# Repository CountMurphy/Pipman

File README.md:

Pipman Propeller watch
======================

The Pipman is a GPS average intelligence (not dumb, but not quit smart like pebble) watch that runs on the propeller platform.  It boasts:

* 1 Gb internal memory (for saving calendar info and saving GPS coordinates)
* GPS (with time syncing abilities, can get local time anywhere in the world)
* Tilt Compensated Compass
* Temperature reader
* Color Screen
* Calendar
* USB support

Note: The current code is beta ( I'm not going to pretend all of it is clean. Some parts are rubbish.  You know it, I know it, lets move on) and hardware specific. It can be easily tweaked to suit your needs, but if you want to create the watch exactly as is the parts are as follows:

* A 4d systems oled-128-G1 (http://old.4dsystems.com.au/prod.php?id=78)  (the G2 should work too)
* Any NEMA Gps (though for the PCB designs I used this one: http://www.mouser.com/ProductDetail/4D-Systems/GPS-PA6B/?qs=0tg2fxsCAusQqyNQtvdH%252bA%3D%3D)
* The Honeywell hmc6343 (http://www.digikey.com/product-detail/en/HMC6343/342-1056-ND/1692480.  If you know how to tweak I2C code it wouldn't be hard to get any compass moduel to work)
* 5 way switch for navigation (http://www.adafruit.com/products/504)

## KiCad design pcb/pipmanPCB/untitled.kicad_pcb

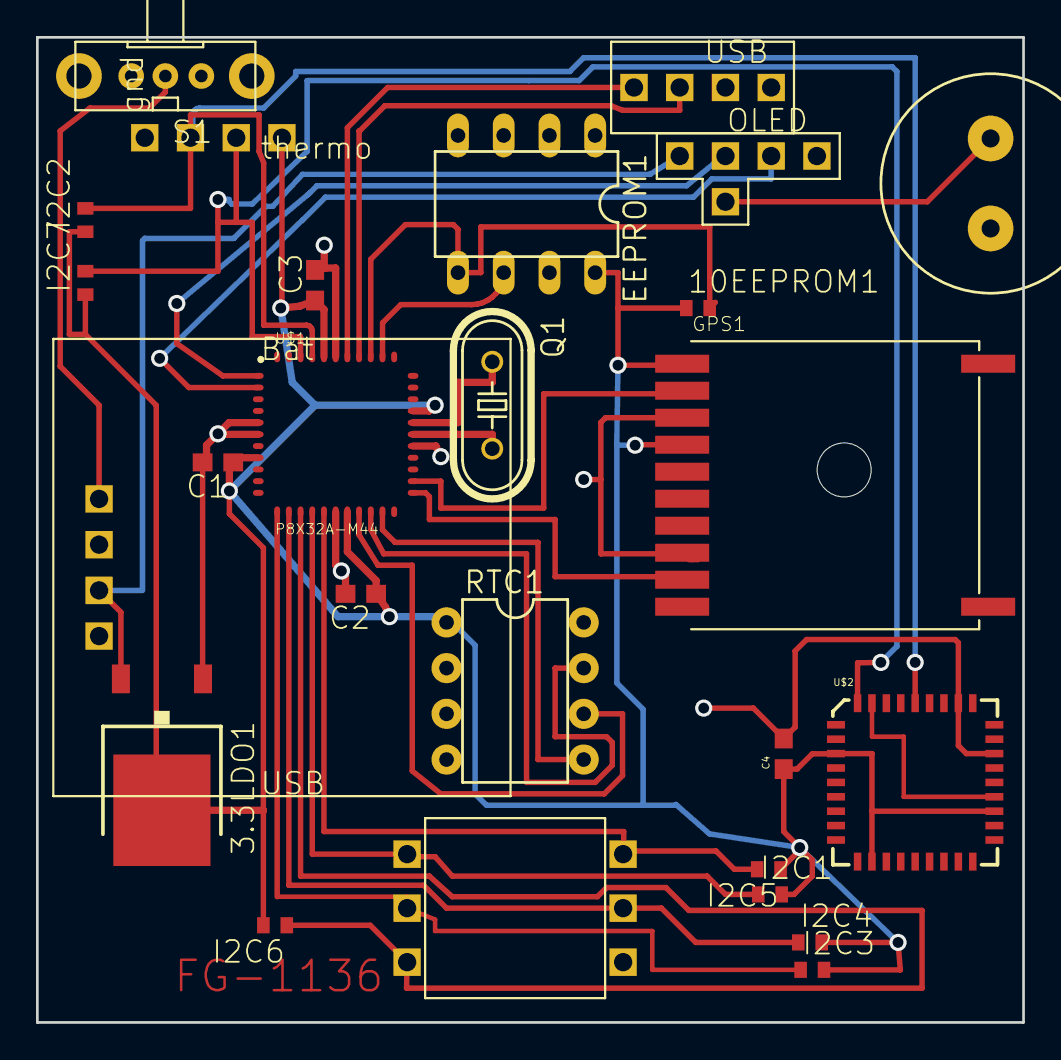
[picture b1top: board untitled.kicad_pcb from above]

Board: 2 copper layers, 54.8 x 54.7 mm, 26 parts (0 on the bottom side), 26 nets.

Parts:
3.3LDO1: REG1117X; TO252
5WAYSWITCH1: 5-WAYSWITCH
10EEPROM1: R-US_R1005; R1005
C1, C2, C3: C-USC0603; C0603
C4: CAP0603; 0603
EEPROM1: DS1307; DIL08
GPS1: GPS_FGPMMOPA6B; FGPMMOPA6B
I2C1, I2C2, I2C3, I2C4, I2C5, I2C6, I2C7: R-US_R1005; R1005
LIPOCHARGER-BOOSTER1: SFLIPO
OLED_SCREEN1: 4DSCREEN
Q1: CRYSTALHC49S; HC49_S
RTC1: DS1302; DIL08-ROUND
S1: EG1213
SP1: SPEAKER_PS12; PS12
THERMO1: SFTEMP
U$1: P8X32A-M44
U$2: HMC6343A; LCC36
USB1: 4PINUSB

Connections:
+3V3: 3.3LDO1.3, 10EEPROM1.1, C1.1, C2.1, C3.1, C4.1, EEPROM1.8, GPS1.P$1, GPS1.P$4, I2C1.2, I2C2.1, I2C3.2, I2C4.2, I2C5.1, I2C6.2, I2C7.1, RTC1.1, THERMO1.VCC, U$1.8, U$1.18, U$1.30, U$1.40, U$2.3, U$2.11, U$2.21
+5V: 3.3LDO1.2, LIPOCHARGER-BOOSTER1.VCC, OLED_SCREEN1.5V
/SCL: I2C2.2, THERMO1.SCL, U$1.41, U$2.32
/SDA: I2C7.2, THERMO1.SDA, U$1.42, U$2.36
GND: 3.3LDO1.1, 5WAYSWITCH1.GND, C1.2, C2.2, C3.2, C4.2, EEPROM1.1, EEPROM1.2, EEPROM1.3, EEPROM1.4, EEPROM1.7, GPS1.P$3, GPS1.P$8, LIPOCHARGER-BOOSTER1.GND, OLED_SCREEN1.GND, RTC1.4, S1.1, SP1.P$2, THERMO1.GND, U$1.5, U$1.6, U$1.17, U$1.27, U$1.39, U$2.25, U$2.29, USB1.VSS
unnamed: 5WAYSWITCH1.BTN, I2C5.2, U$1.16
unnamed: 5WAYSWITCH1.D, I2C6.1, U$1.14
unnamed: 5WAYSWITCH1.L, I2C3.1, U$1.12
unnamed: 5WAYSWITCH1.R, I2C4.1, U$1.13
unnamed: 5WAYSWITCH1.U, I2C1.1, U$1.15
unnamed: 10EEPROM1.2, EEPROM1.5, U$1.36
unnamed: EEPROM1.6, U$1.35
unnamed: GPS1.P$2, U$1.24
unnamed: GPS1.P$9, U$1.23
unnamed: LIPOCHARGER-BOOSTER1.EN, S1.2
unnamed: OLED_SCREEN1.PEZ, SP1.P$1
unnamed: OLED_SCREEN1.RX, U$1.2
unnamed: OLED_SCREEN1.TX, U$1.1
unnamed: Q1.1, U$1.29
unnamed: Q1.2, U$1.28
unnamed: RTC1.5, U$1.21
unnamed: RTC1.6, U$1.19
unnamed: RTC1.7, U$1.20
unnamed: U$1.37, USB1.TX
unnamed: U$1.38, USB1.RX
unnamed: U$2.22, U$2.35

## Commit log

2012-11-24 added
2012-11-24 added extra bool for track ball detection, renamed file
2012-11-27 fixed typo
2012-12-10 Created clock obj
2012-12-11 added rtc code
2012-12-16 added gps code
2012-12-31 gps on / off /serial working
2013-01-01 serial kind of working
2013-01-13 Can now successfully read gps data
2013-01-27 added sat logic
2013-01-27 Sat count fully working. strToDec Completed
2013-02-03 found a round about way to convert strings to floats. all gps follow this pattern, 0000.0000
2013-02-21 Region detection working
2013-02-25 Region detection code working
2013-03-17 Finished GPS conversion method
2013-04-23 Compass code completed
2013-04-23 removed unused files
2013-05-06 Added DOW conversion
2013-05-06 added untested compass power modes. Will test when bst stops being a bitch
2013-06-09 Completed Screen driver
2013-06-17 Created Menu System
    Added temperature code. renamed compass.spin to sensors
2013-06-26 Tweaked menu system and created main clock page
2013-06-29 Manual date time setting done
2013-07-06 Finished Stop watch and timer
2013-07-19 Read / write code done. GPS code done
2013-07-29 Auto date / time setting done. DST support done
2013-07-30 forgot to uncomment fade code
2013-07-30 added wait for debugging display
2013-08-11 fixed serial extra cog bug
2013-08-12 changed images on SD card
    added
2013-08-13 Added spinner video for inital load, plays by frames for gps single and google
2013-08-19 Created Comm menu and finished all export code
2013-09-28 Finished All Import Code and started work on Cal
2013-09-29 fixed date time bug
2013-09-29 Added Calendar Feature and Calendar Alarms
2013-09-29 Fixed Various Calendar bugs
2013-09-29 Added sound code that is actually useful
2013-10-08 Fixed broken GPS tracking code
2013-10-13 Added GPS calibrate cancalation and removed redundant code
2013-10-13 Added Time to timer and fixed various timer bugs
2013-10-14 fixed display bug for displaying debug info
2013-10-14 fixed broken altitude.
2014-02-24 fixed syntax error that lead to date display error
2014-06-11 fixed bug in google display?
2014-06-13 5way switch added to replace trackball
2014-06-13 think I really fixed the bug without ignoring edge case
2014-08-17 added readme
2014-08-17 updated for hackaday space contest
2014-10-05 Added del calendar, added 2 second wait on boot, fixed google maps bug
2014-11-28 Added click to menus
2014-12-21 Reversed screen pins because I'm a noob and cant PCB
2015-01-02 frist round of GPS changes
2015-01-04 added splash screen
2015-01-11 changed baud, added error checks. Fixed parse issue
2015-01-11 removed redundant check
2015-01-11 added checks for valid gps data. still unsure how data gets corrupted. Will research more
2015-01-11 fixed audio notify
2015-01-11 removed dead code
2015-01-13 fixed gps menu bugs introduced in last commit
2015-05-23 Steinds;Gate reference for lulz
2015-09-05 added dbad license
2015-11-03 fixed noise on serial lines
2015-11-03 added theatre mode
2016-02-27 wont turn screen on until gps work is done
2016-02-27 added more error checking to prevent manual restart
2016-02-27 upreved
2016-02-28 fix faulty lon error check code
2018-07-17 added PCB in kicad
2019-10-14 screwed up last commit and commited empty files
